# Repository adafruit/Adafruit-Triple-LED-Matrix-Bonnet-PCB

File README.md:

## Adafruit Triple LED Matrix Bonnet for Raspberry Pi - For HUB75 PCB

<a href="http://www.adafruit.com/products/6358"><br/>
Click here to purchase one from the Adafruit shop</a>

PCB files for the Adafruit Triple LED Matrix Bonnet for Raspberry Pi - For HUB75. 

Format is EagleCAD schematic and board layout
* https://www.adafruit.com/product/6358

### Description

You can now create large, dazzling LED matrix displays with your Raspberry Pi with the Adafruit Triple Matrix Bonnet for Raspberry Pi. This boards plugs into your Raspberry Pi with 2x20 header, and makes it super easy to control three parallel strings of HUB75 RGB matrices such as those we stock in the shop and create colorful scrolling displays or mini LED walls with ease. 

[Unlike our single-panel Matrix Bonnet](https://www.adafruit.com/product/3211), this board can drive 3 panels in parallel, also known as "active3" pinout. This means it can handle approximately 3x as many panels/pixels. However, as a trade-off, the power management is not done on-board. Instead you will have to provide the 5V 10A+ power separately! [We recommend two power distribution bus bars](https://www.adafruit.com/product/737), they're good for many amps and make wiring easier.

* "Bonnet" boards work on Raspberry Pi with a 40-pin GPIO header — Zero, Zero W/WH, Model A+, B+, Pi 2, Pi 3, Pi 4, Pi 5 They do not work with older 26-pin boards like the original Model A or B. Note with the Pi Zero, you may need to solder a header on the Pi board; it’s normally unpopulated on that model. For best performance we recommend a Pi 4 or Pi 5.
* For Pi 0, 2, 3, and 4 we recommend the [rpi-rgb-matrix driver](https://github.com/hzeller/rpi-rgb-led-matrix), with C and Python bindings. It works great, just select the standard/active3 pinout.
* For Pi 5+, [we recommend using our PIO-based matrix driver](https://learn.adafruit.com/rgb-matrix-panels-with-raspberry-pi-5) which supports up to 3 panels - check the guide for the demo code for the triple bonnet
* By default the bonnet has a slim 2x20 header on it. If you need to 'lift' the bonnet above an enclosure, [pick up a 2x20 riser header](https://www.adafruit.com/product/4079). 
* If you want to get access to GPIO while the bonnet is installed, [pick up a 2x20 stacking header](https://www.adafruit.com/product/2223) - the pins will slide through the socket and you can plug something else on top.

This bonnet will make your mega-matrix projects super easy and avoid wiring complexity and mistakes:

* Simple design - plug in IDC cables, provide separate power to each panel, run our Python code!
* Onboard level shifters to convert the RasPi's 3.3V to 5.0V logic for clean and glitch free matrix driving
* Fully assembled compact design no soldering required! Plugs onto any Raspberry Pi with a 2x20 connector, and you're ready to glow.

Works with any of our [16x32, 32x32, 32x64, or 64x64 RGB LED Matrices with HUB75 connections](https://www.adafruit.com/categories/327). When using with 64x64 you can select whether the Address E pin is on the 4'th or 8'th IDC pad with an on-board switch. Want even more lights? No problem, chain multiple matrices together for a longer display. The bigger the display the harder it is on the Pi, so keep that in mind if you're using a lower-powered Pi Zero.

Please note: this Bonnet is only for use with HUB75 type RGB matrices. Not for use with NeoPixel, DotStar, or other 'addressable' LEDs.

Each order comes with a fully assembled and ready to go bonnet with all parts assembled. [RGB Matrix is not included, please check out our fine selection](https://www.adafruit.com/categories/327).

A serious 5V power supply is also required, not included, for power the matrix itself; the Pi cannot do it, to calculate the power, multiply the width of all the chained matrices * 0.12 Amps : A 32 pixel wide matrix can end up drawing 32*0.12 = 3.85A per panel so we recommend [a 5V 10A power supply](https://www.adafruit.com/product/658). Actual power usage will vary with how many LEDs you light up at once.

Raspberry Pi not included [(but we have 'em in the shop so pick one up! Pi 5 is recommended as its the newest, but Pi 4 will also work well)](https://www.adafruit.com/categories/176)

### License

Adafruit invests time and resources providing this open source design, please support Adafruit and open-source hardware by purchasing products from [Adafruit](https://www.adafruit.com)!

Designed by Limor Fried/Ladyada for Adafruit Industries.

Creative Commons Attribution/Share-Alike, all text above must be included in any redistribution. 
See license.txt for additional details.

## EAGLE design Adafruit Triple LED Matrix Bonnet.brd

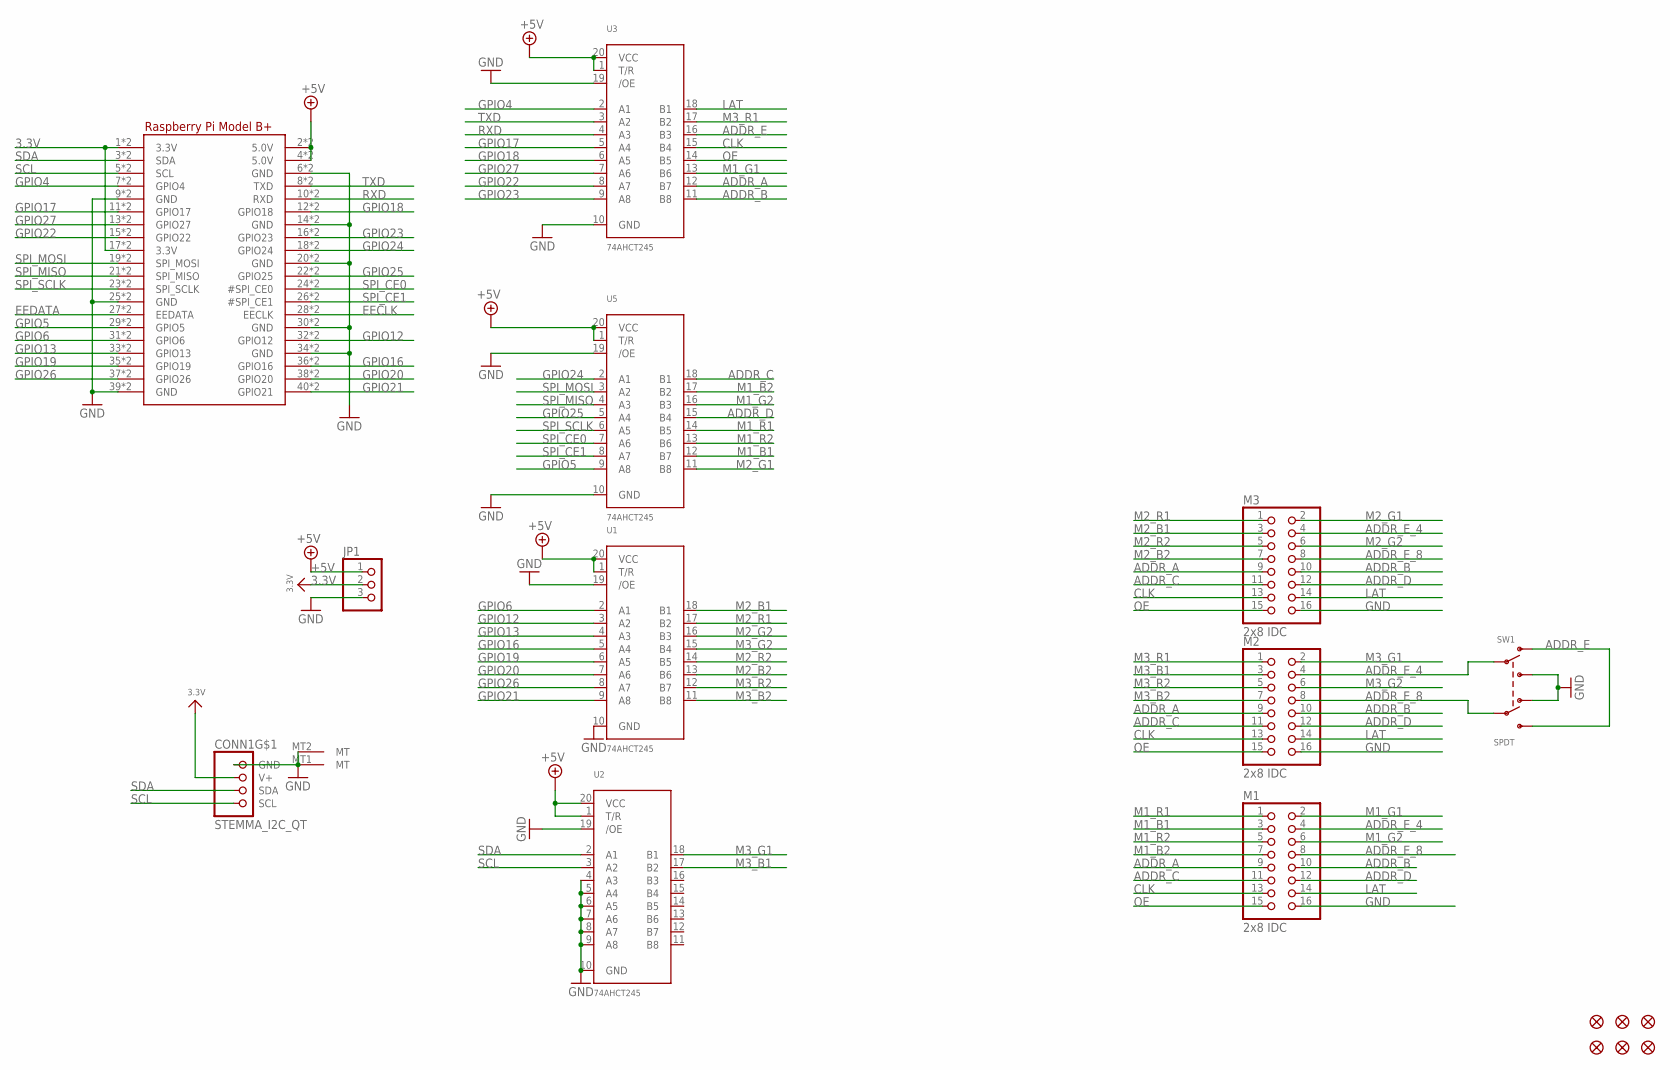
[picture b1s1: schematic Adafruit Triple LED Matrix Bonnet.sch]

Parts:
CONN1: STEMMA_I2C_QT; JST_SH4
FID1, FID2, FID3, FID4, FID5, FID6: FIDUCIAL_1MM
JP1: HEADER-1X376MIL; 1X03_ROUND_76
M1, M2, M3: 2x8 IDC; 2X08_SHROUDED
RPI1: RASPBERRYPI_BPLUS_2X20_THMSMT; RASPI_2X20_THMSMT
SW1: SPDT; EG1390
U1, U2, U3, U5: 74AHCT245; TSSOP20

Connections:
3.3V: CONN1.2 (V+), JP1.2, RPI1.1 (3.3V), RPI1.17 (3.3V), RPI1.S1 (3.3V), RPI1.S17 (3.3V)
+5V: JP1.1, RPI1.2 (5.0V), RPI1.4 (5.0V), RPI1.S2 (5.0V), RPI1.S4 (5.0V), U1.1 (T/R), U1.20 (VCC), U2.1 (T/R), U2.20 (VCC), U3.1 (T/R), U3.20 (VCC), U5.1 (T/R), U5.20 (VCC)
ADDR_A: M1.9, M2.9, M3.9, U3.12 (B7)
ADDR_B: M1.10, M2.10, M3.10, U3.11 (B8)
ADDR_C: M1.11, M2.11, M3.11, U5.18 (B1)
ADDR_D: M1.12, M2.12, M3.12, U5.15 (B4)
ADDR_E: SW1.O1, SW1.S2, U3.16 (B3)
ADDR_E_4: M1.4, M2.4, M3.4, SW1.P1
ADDR_E_8: M1.8, M2.8, M3.8, SW1.P2
CLK: M1.13, M2.13, M3.13, U3.15 (B4)
EECLK: RPI1.28 (EECLK), RPI1.S28 (EECLK)
EEDATA: RPI1.27 (EEDATA), RPI1.S27 (EEDATA)
GND: CONN1.1 (GND), CONN1.MT1 (MT), CONN1.MT2 (MT), JP1.3, M1.16, M2.16, M3.16, RPI1.6 (GND), RPI1.9 (GND), RPI1.14 (GND), RPI1.20 (GND), RPI1.25 (GND), RPI1.30 (GND), RPI1.34 (GND), RPI1.39 (GND), RPI1.S6 (GND), RPI1.S9 (GND), RPI1.S14 (GND), RPI1.S20 (GND), RPI1.S25 (GND), RPI1.S30 (GND), RPI1.S34 (GND), RPI1.S39 (GND), SW1.O2, SW1.S1, U1.10 (GND), U1.19 (/OE), U2.4 (A3), U2.5 (A4), U2.6 (A5), U2.7 (A6), U2.8 (A7), U2.9 (A8), U2.10 (GND), U2.19 (/OE), U3.10 (GND), U3.19 (/OE), U5.10 (GND), U5.19 (/OE)
GPIO4: RPI1.7 (GPIO4), RPI1.S7 (GPIO4), U3.2 (A1)
GPIO5: RPI1.29 (GPIO5), RPI1.S29 (GPIO5), U5.9 (A8)
GPIO6: RPI1.31 (GPIO6), RPI1.S31 (GPIO6), U1.2 (A1)
GPIO12: RPI1.32 (GPIO12), RPI1.S32 (GPIO12), U1.3 (A2)
GPIO13: RPI1.33 (GPIO13), RPI1.S33 (GPIO13), U1.4 (A3)
GPIO16: RPI1.36 (GPIO16), RPI1.S36 (GPIO16), U1.5 (A4)
GPIO17: RPI1.11 (GPIO17), RPI1.S11 (GPIO17), U3.5 (A4)
GPIO18: RPI1.12 (GPIO18), RPI1.S12 (GPIO18), U3.6 (A5)
GPIO19: RPI1.35 (GPIO19), RPI1.S35 (GPIO19), U1.6 (A5)
GPIO20: RPI1.38 (GPIO20), RPI1.S38 (GPIO20), U1.7 (A6)
GPIO21: RPI1.40 (GPIO21), RPI1.S40 (GPIO21), U1.9 (A8)
GPIO22: RPI1.15 (GPIO22), RPI1.S15 (GPIO22), U3.8 (A7)
GPIO23: RPI1.16 (GPIO23), RPI1.S16 (GPIO23), U3.9 (A8)
GPIO24: RPI1.18 (GPIO24), RPI1.S18 (GPIO24), U5.2 (A1)
GPIO25: RPI1.22 (GPIO25), RPI1.S22 (GPIO25), U5.5 (A4)
GPIO26: RPI1.37 (GPIO26), RPI1.S37 (GPIO26), U1.8 (A7)
GPIO27: RPI1.13 (GPIO27), RPI1.S13 (GPIO27), U3.7 (A6)
LAT: M1.14, M2.14, M3.14, U3.18 (B1)
M1_B1: M1.3, U5.12 (B7)
M1_B2: M1.7, U5.17 (B2)
M1_G1: M1.2, U3.13 (B6)
M1_G2: M1.6, U5.16 (B3)
M1_R1: M1.1, U5.14 (B5)
M1_R2: M1.5, U5.13 (B6)
M2_B1: M3.3, U1.18 (B1)
M2_B2: M3.7, U1.13 (B6)
M2_G1: M3.2, U5.11 (B8)
M2_G2: M3.6, U1.16 (B3)
M2_R1: M3.1, U1.17 (B2)
M2_R2: M3.5, U1.14 (B5)
M3_B1: M2.3, U2.17 (B2)
M3_B2: M2.7, U1.11 (B8)
M3_G1: M2.2, U2.18 (B1)
M3_G2: M2.6, U1.15 (B4)
M3_R1: M2.1, U3.17 (B2)
M3_R2: M2.5, U1.12 (B7)
OE: M1.15, M2.15, M3.15, U3.14 (B5)
RXD: RPI1.10 (RXD), RPI1.S10 (RXD), U3.4 (A3)
SCL: CONN1.4 (SCL), RPI1.5 (SCL), RPI1.S5 (SCL), U2.3 (A2)
SDA: CONN1.3 (SDA), RPI1.3 (SDA), RPI1.S3 (SDA), U2.2 (A1)
SPI_CE0: RPI1.24 (#SPI_CE0), RPI1.S24 (#SPI_CE0), U5.7 (A6)
SPI_CE1: RPI1.26 (#SPI_CE1), RPI1.S26 (#SPI_CE1), U5.8 (A7)
SPI_MISO: RPI1.21 (SPI_MISO), RPI1.S21 (SPI_MISO), U5.4 (A3)
SPI_MOSI: RPI1.19 (SPI_MOSI), RPI1.S19 (SPI_MOSI), U5.3 (A2)
SPI_SCLK: RPI1.23 (SPI_SCLK), RPI1.S23 (SPI_SCLK), U5.6 (A5)
TXD: RPI1.8 (TXD), RPI1.S8 (TXD), U3.3 (A2)

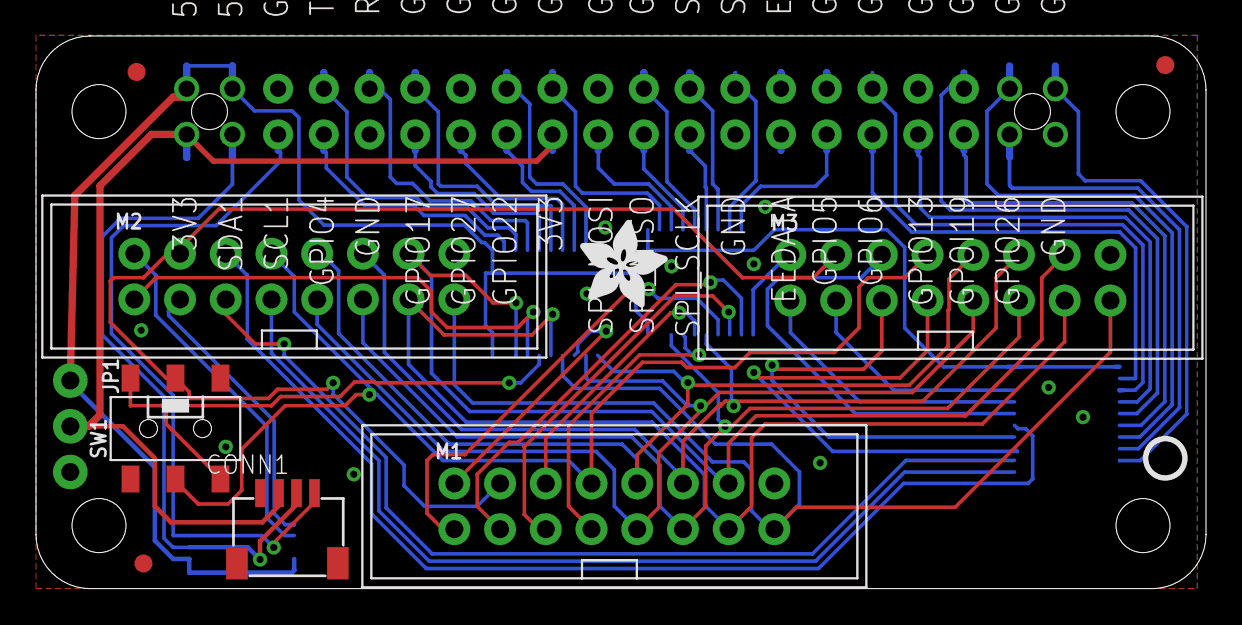
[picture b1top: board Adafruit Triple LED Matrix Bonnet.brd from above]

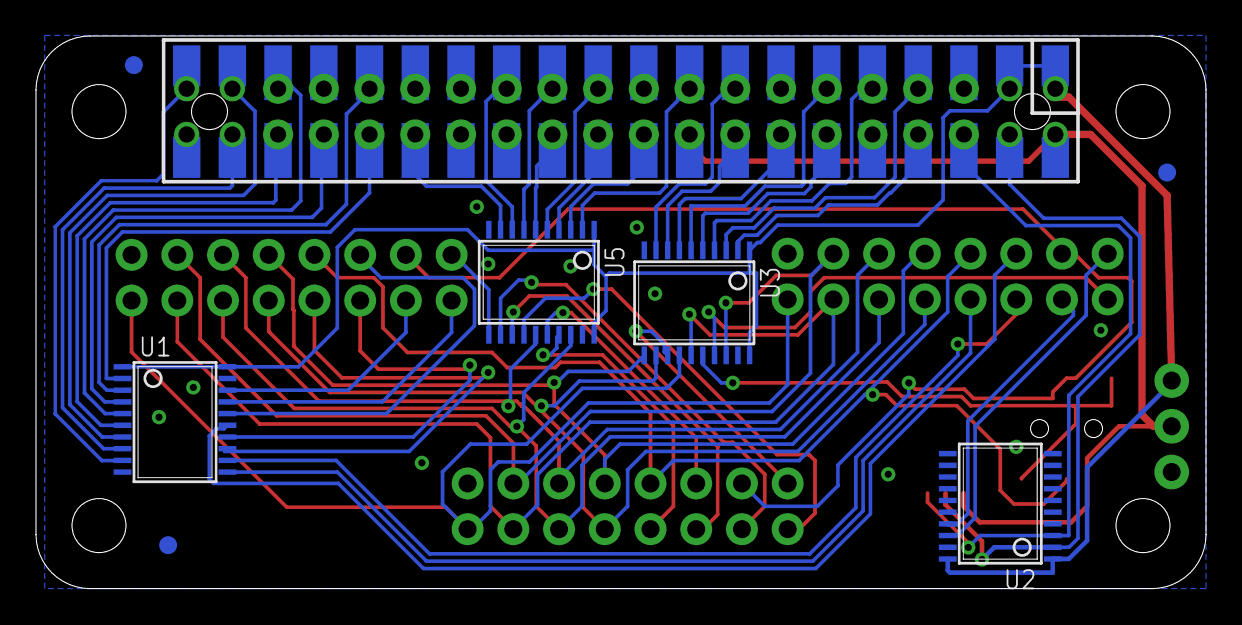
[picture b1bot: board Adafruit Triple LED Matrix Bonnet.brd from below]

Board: 2 copper layers, 65.0 x 30.7 mm, 84 parts (61 on the bottom side), 59 nets.

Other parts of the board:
PLABEL0: PLABEL0
PLABEL1: PLABEL1
PLABEL2: PLABEL2
PLABEL3: PLABEL3
PLABEL4: PLABEL4
PLABEL5: PLABEL5
PLABEL6: PLABEL6
PLABEL7: PLABEL7
PLABEL8: PLABEL8
PLABEL9: PLABEL9
PLABEL10: PLABEL10
PLABEL11: PLABEL11
PLABEL12: PLABEL12
PLABEL13: PLABEL13
PLABEL14: PLABEL14
PLABEL15: PLABEL15
PLABEL16: PLABEL16
PLABEL17: PLABEL17
PLABEL18: PLABEL18
PLABEL19: PLABEL19
PLABEL20: PLABEL20
PLABEL21: PLABEL21
PLABEL22: PLABEL22
PLABEL23: PLABEL23
PLABEL24: PLABEL24
PLABEL25: PLABEL25
PLABEL26: PLABEL26
PLABEL27: PLABEL27
PLABEL28: PLABEL28
PLABEL29: PLABEL29
PLABEL30: PLABEL30
PLABEL31: PLABEL31
PLABEL32: PLABEL32
PLABEL33: PLABEL33
PLABEL34: PLABEL34
PLABEL35: PLABEL35
PLABEL36: PLABEL36
PLABEL37: PLABEL37
PLABEL38: PLABEL38
PLABEL39: PLABEL39
PLABEL40: PLABEL40
PLABEL41: PLABEL41
PLABEL42: PLABEL42
PLABEL43: PLABEL43
PLABEL44: PLABEL44
PLABEL45: PLABEL45
PLABEL46: PLABEL46
PLABEL47: PLABEL47
PLABEL48: PLABEL48
PLABEL49: PLABEL49
PLABEL50: PLABEL50
PLABEL51: PLABEL51
PLABEL52: PLABEL52
PLABEL53: PLABEL53
PLABEL54: PLABEL54
PLABEL55: PLABEL55
PLABEL56: PLABEL56
PLABEL57: PLABEL57
PLABEL58: PLABEL58
PLABEL59: PLABEL59
PLABEL60: PLABEL60
PLABEL61: PLABEL61
PLABEL62: PLABEL62
PLABEL63: PLABEL63
PLABEL64: PLABEL64
U$2: ADAFRUIT_5MM
U$3: PCBFEAT-REV-056

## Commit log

2025-07-08 cookiecutter

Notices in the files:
parts and their libraries:
microbuilder: This work is placed in the public domain, and may be freely used for commercial and non-commercial work with the following conditions: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
